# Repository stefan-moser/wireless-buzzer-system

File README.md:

# Wireless Buzzer System

## Features
- Standalone Wireless Buzzer System - One Host, Four Buzzers
- 2.4GHz Wireless Transmission
- Statefull Game, the Host-Station controls the game
- Memory-Function, the Host-Station is able to remember button presses

## Installation
The project was built using VSCode and PlattformIO and
it uses external librarys, pls clone with
`--recurse-submodules`.

## Credits
The project is based on the [Wireless Game Show Buzzer](https://github.com/mudmin/AnotherMaker/tree/master/gameshow "Wireless Game Show Buzzer") from [AnotherMaker](https://www.youtube.com/AnotherMaker "AnotherMaker").
- [RF24 library](https://github.com/nRF24/RF24 "RF24 library") - Used for wireless transmission

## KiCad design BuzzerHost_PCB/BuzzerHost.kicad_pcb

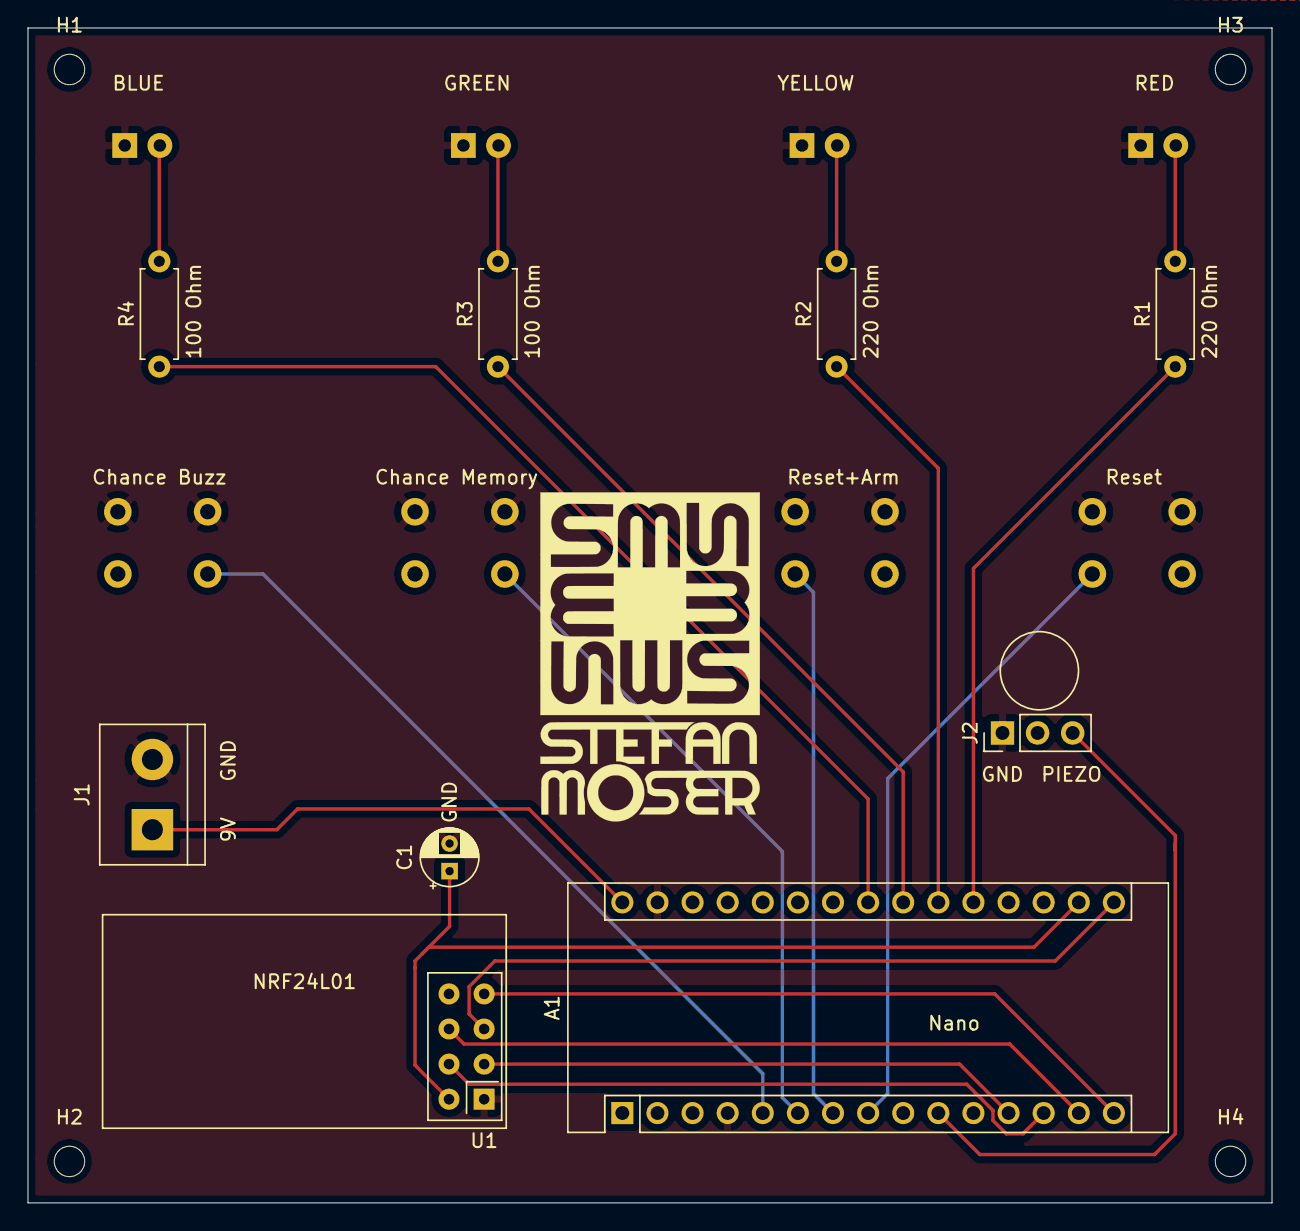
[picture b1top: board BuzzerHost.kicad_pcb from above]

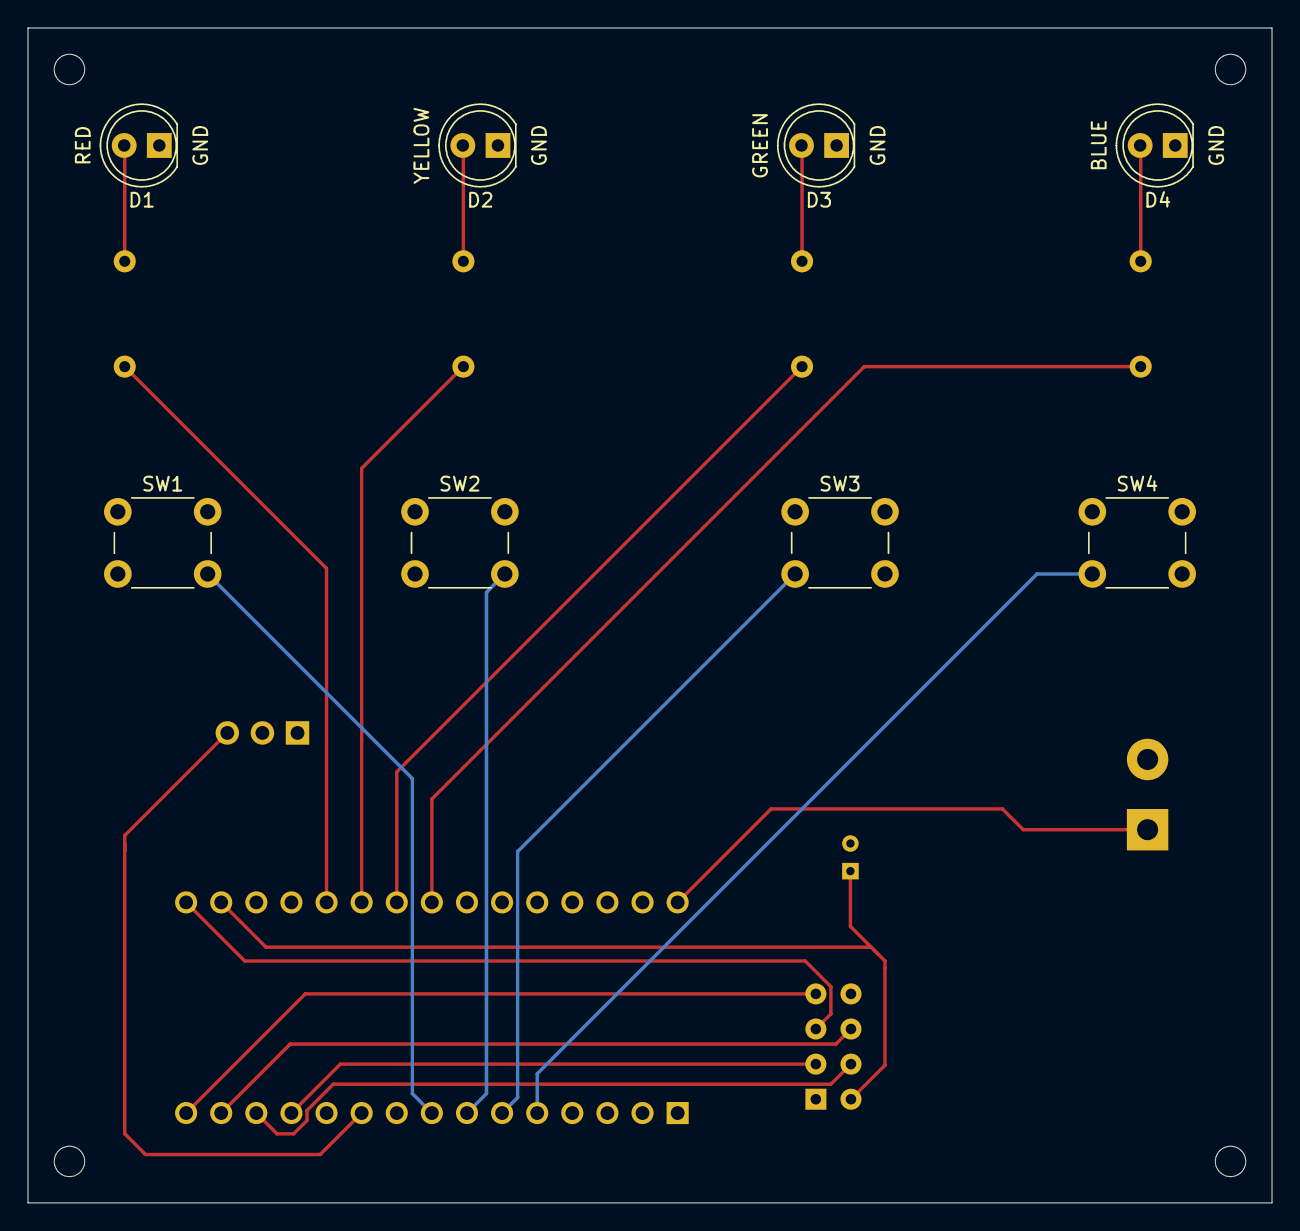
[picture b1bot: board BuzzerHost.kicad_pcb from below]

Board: 2 copper layers, 90.0 x 85.0 mm, 21 parts (8 on the bottom side), 21 nets.

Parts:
A1: Arduino_Nano_v2.x; Arduino_Nano
C1: CP; CP_Radial_D4.0mm_P2.00mm
D1, D2, D3, D4: LED; LED_D5.0mm
H1, H2, H3, H4: MountingHole; MountingHole_2.2mm_M2
J1: Screw_Terminal_01x02; TerminalBlock_bornier-2_P5.08mm
J2: Conn_01x03_Female; PinHeader_1x03_P2.54mm_Vertical
R1, R2, R3, R4: R; R_Axial_DIN0207_L6.3mm_D2.5mm_P7.62mm_Horizontal
SW1, SW2, SW3, SW4: SW_Push_Dual; SW_PUSH_6mm_H13mm
U1: NRF24L01_Breakout; nRF24L01_Breakout

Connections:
+9V: A1.30, J1.1
GND: A1.4, A1.29, C1.2, D1.1, D2.1, D3.1, D4.1, J1.2, J2.1, SW1.1, SW2.1, SW3.1, SW4.1, U1.1
unnamed: A1.5, SW4.2
unnamed: A1.6, SW3.2
unnamed: A1.7, SW2.2
unnamed: A1.8, SW1.2
unnamed: A1.10, J2.3
unnamed: A1.12, U1.3
unnamed: A1.13, U1.4
unnamed: A1.14, U1.6
unnamed: A1.15, U1.7
unnamed: A1.16, U1.5
unnamed: A1.17, C1.1, U1.2
unnamed: A1.20, R1.1
unnamed: A1.21, R2.1
unnamed: A1.22, R3.1
unnamed: A1.23, R4.1
unnamed: D1.2, R1.2
unnamed: D2.2, R2.2
unnamed: D3.2, R3.2
unnamed: D4.2, R4.2

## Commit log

2022-05-07 initial project upload
2022-05-07 Update README.md again
    im learning ...
